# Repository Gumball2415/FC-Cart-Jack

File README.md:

# FC Cartridge Audio Jack

An audio jack output for unmodified RF Famicom systems.

## Instructions for installation

Upcoming!

## PCB Specifications

Note that this project is optimized for JLCPCB manufacturing, so you may have to modify the gerber export, remove the "JLCJLCJLCJLC" silkscreen text, etc.

- 2 layers
- 97.0mm x 64.3mm
- 1.2mm thickness
- ENIG-RoHS surface finish recommended; Gold fingers optional
- dark silkscreen, light soldermask

## License

The PCB and schematics are licensed under the [TAPR Open Hardware License](https://tapr.org/the-tapr-open-hardware-license/). © Persune 2022

## Credits

- [@N-SPC700](https://github.com/N-SPC700) for suggesting this idea
- [@Lockster-Inc](https://github.com/Lockster-Inc) for the wonderful silkscreen art
- lidnariq, Finny: advice for terminating audio output
- Finny: buffer circuit design, based on reverse engineered RF modulator schematics
- Special thanks to the NESDEV community, this project wouldn't have been possible without their extensive help and wiki.

## Support

If you enjoy this project or find it helpful, please support me on [Ko-Fi](https://ko-fi.com/persune) or [Patreon](https://www.patreon.com/persune)!

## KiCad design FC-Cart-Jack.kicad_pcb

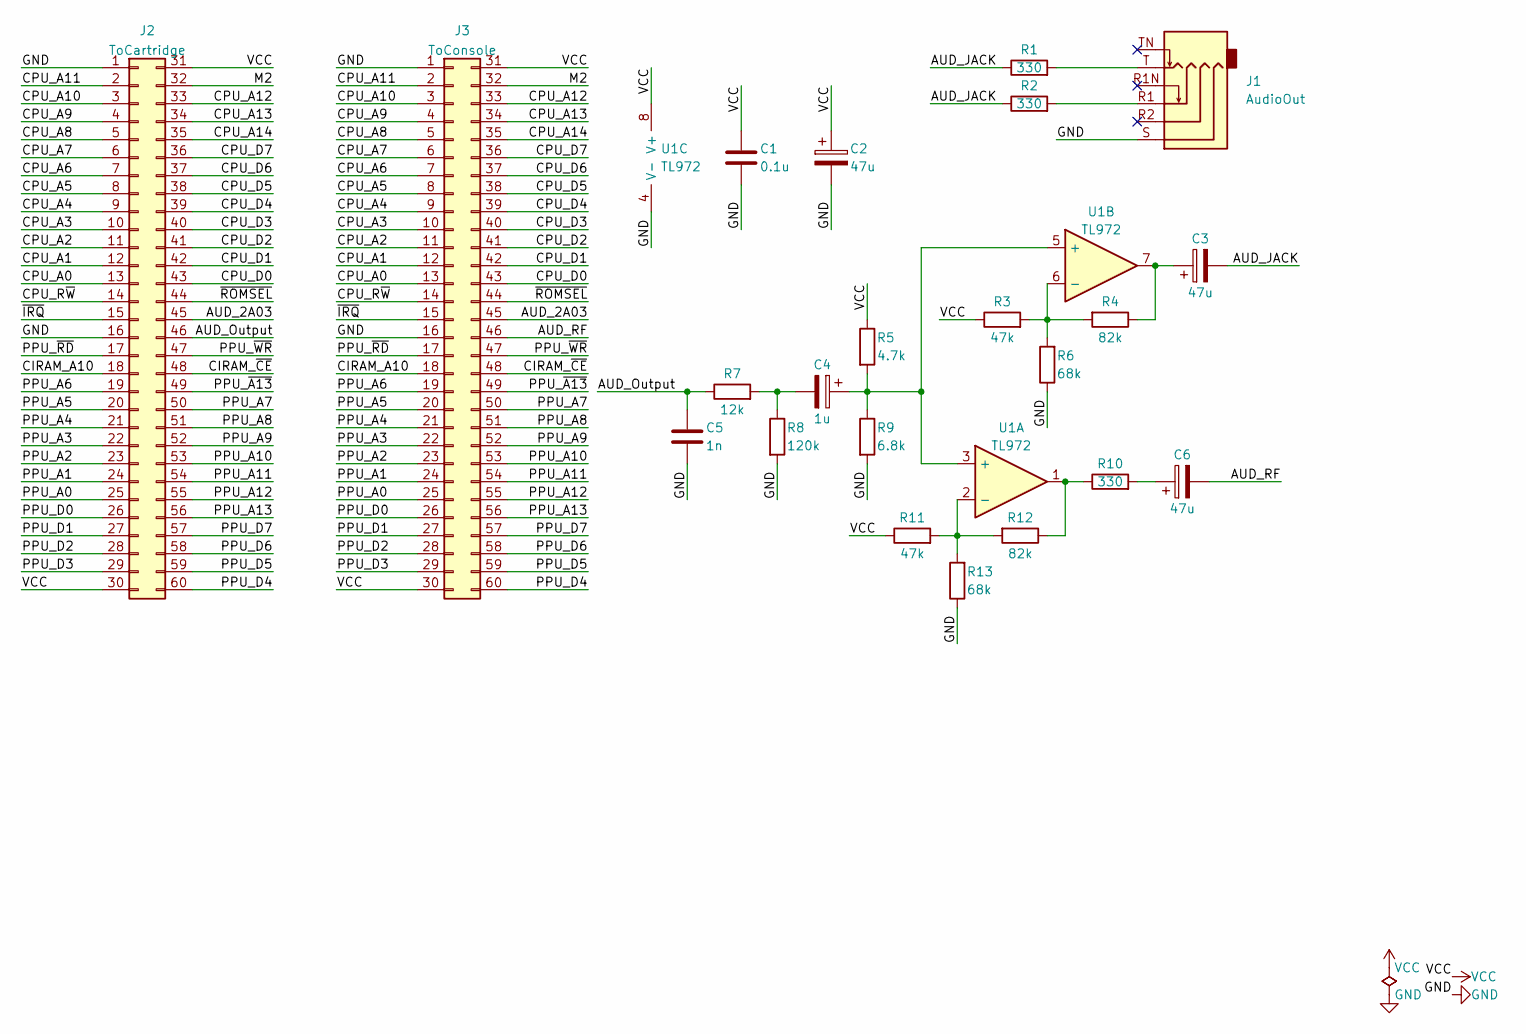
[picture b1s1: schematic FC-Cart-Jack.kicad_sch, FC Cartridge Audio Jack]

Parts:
C1: 0.1u; C_0805_2012Metric
C2, C3, C6: 47u; CP_Elec_5x5.4
C4: 1u; CP_Elec_4x5.4
C5: 1n; C_0805_2012Metric
J1: AudioOut; Jack_3.5mm_PJ-342B-TX-SMT
J2: ToCartridge; FC_CONN_F
J3: ToConsole; HVC-TGROM-01
R1, R2, R10: 330; R_0805_2012Metric
R3, R11: 47k; R_0805_2012Metric
R4, R12: 82k; R_0805_2012Metric
R5: 4.7k; R_0805_2012Metric
R6, R13: 68k; R_0805_2012Metric
R7: 12k; R_0805_2012Metric
R8: 120k; R_0805_2012Metric
R9: 6.8k; R_0805_2012Metric
U1: TL972; SO-8_3.9x4.9mm_P1.27mm

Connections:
/AUD_2A03: J2.45, J3.45
/AUD_JACK: C3.2, R1.1, R2.1
/AUD_Output: C5.1, J2.46, R7.1
/AUD_RF: C6.2, J3.46
/CIRAM_A10: J2.18, J3.18
/CIRAM_~CE: J2.48, J3.48
/CPU_A0: J2.13, J3.13
/CPU_A1: J2.12, J3.12
/CPU_A2: J2.11, J3.11
/CPU_A3: J2.10, J3.10
/CPU_A4: J2.9, J3.9
/CPU_A5: J2.8, J3.8
/CPU_A6: J2.7, J3.7
/CPU_A7: J2.6, J3.6
/CPU_A8: J2.5, J3.5
/CPU_A9: J2.4, J3.4
/CPU_A10: J2.3, J3.3
/CPU_A11: J2.2, J3.2
/CPU_A12: J2.33, J3.33
/CPU_A13: J2.34, J3.34
/CPU_A14: J2.35, J3.35
/CPU_D0: J2.43, J3.43
/CPU_D1: J2.42, J3.42
/CPU_D2: J2.41, J3.41
/CPU_D3: J2.40, J3.40
/CPU_D4: J2.39, J3.39
/CPU_D5: J2.38, J3.38
/CPU_D6: J2.37, J3.37
/CPU_D7: J2.36, J3.36
/CPU_R~W: J2.14, J3.14
/M2: J2.32, J3.32
/PPU_A0: J2.25, J3.25
/PPU_A1: J2.24, J3.24
/PPU_A2: J2.23, J3.23
/PPU_A3: J2.22, J3.22
/PPU_A4: J2.21, J3.21
/PPU_A5: J2.20, J3.20
/PPU_A6: J2.19, J3.19
/PPU_A7: J2.50, J3.50
/PPU_A8: J2.51, J3.51
/PPU_A9: J2.52, J3.52
/PPU_A10: J2.53, J3.53
/PPU_A11: J2.54, J3.54
/PPU_A12: J2.55, J3.55
/PPU_A13: J2.56, J3.56
/PPU_D0: J2.26, J3.26
/PPU_D1: J2.27, J3.27
/PPU_D2: J2.28, J3.28
/PPU_D3: J2.29, J3.29
/PPU_D4: J2.60, J3.60
/PPU_D5: J2.59, J3.59
/PPU_D6: J2.58, J3.58
/PPU_D7: J2.57, J3.57
/PPU_~A13: J2.49, J3.49
/PPU_~RD: J2.17, J3.17
/PPU_~WR: J2.47, J3.47
/~IRQ: J2.15, J3.15
/~ROMSEL: J2.44, J3.44
GND: C1.2, C2.2, C5.2, J1.S, J2.1, J2.16, J3.1, J3.16, R6.1, R8.2, R9.2, R13.1, U1.4 (V-)
unnamed: C3.1, R4.1, U1.7
unnamed: C4.2, R7.2, R8.1
unnamed: C6.1, R10.2
unnamed: J1.R1, R2.2
unnamed: J1.T, R1.2
unnamed: R10.1, R12.1, U1.1
unnamed: C4.1, R5.2, R9.1, U1.3 (+), U1.5 (+)
unnamed: R11.2, R12.2, R13.2, U1.2 (-)
unnamed: R3.2, R4.2, R6.2, U1.6 (-)
VCC: C1.1, C2.1, J2.30, J2.31, J3.30, J3.31, R3.1, R5.1, R11.1, U1.8 (V+)

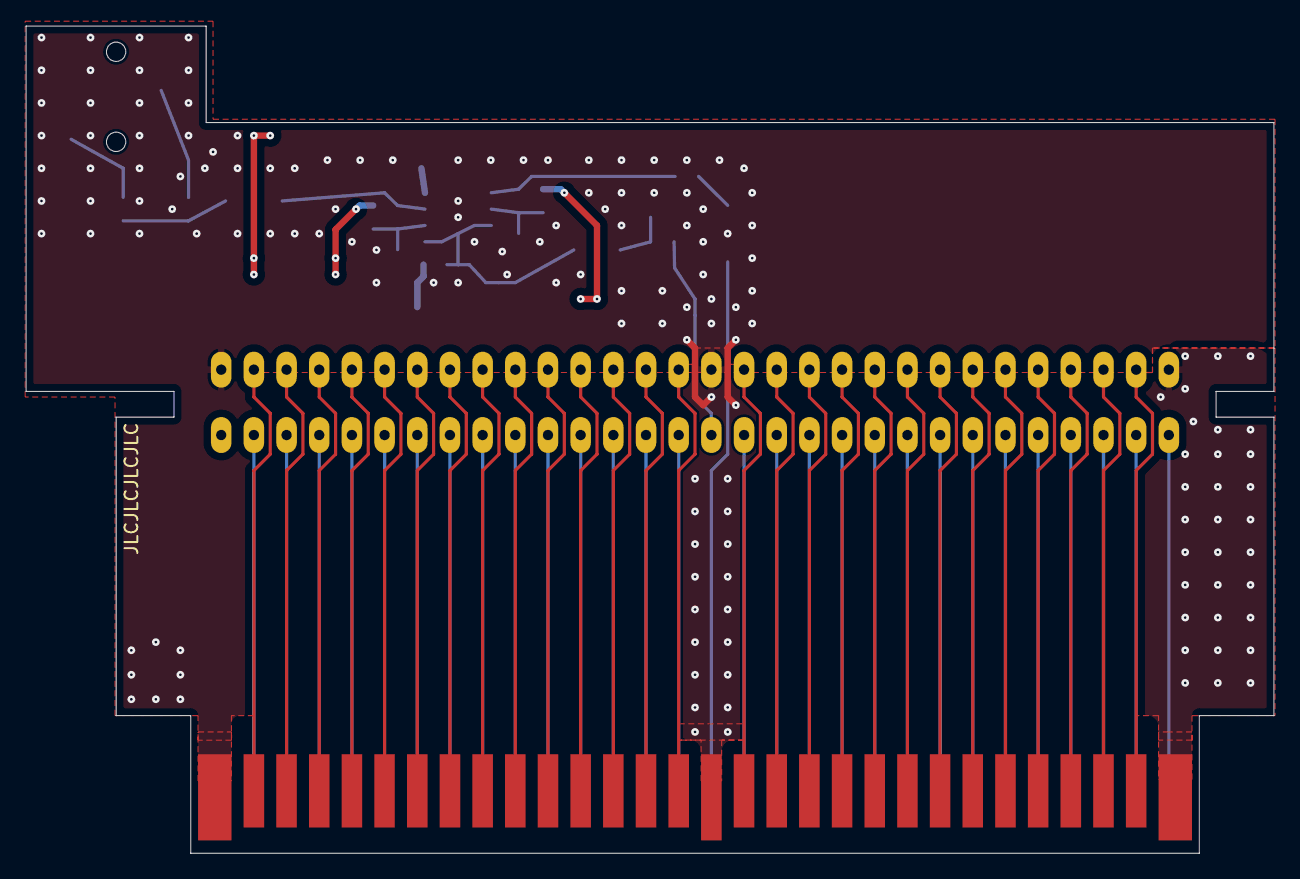
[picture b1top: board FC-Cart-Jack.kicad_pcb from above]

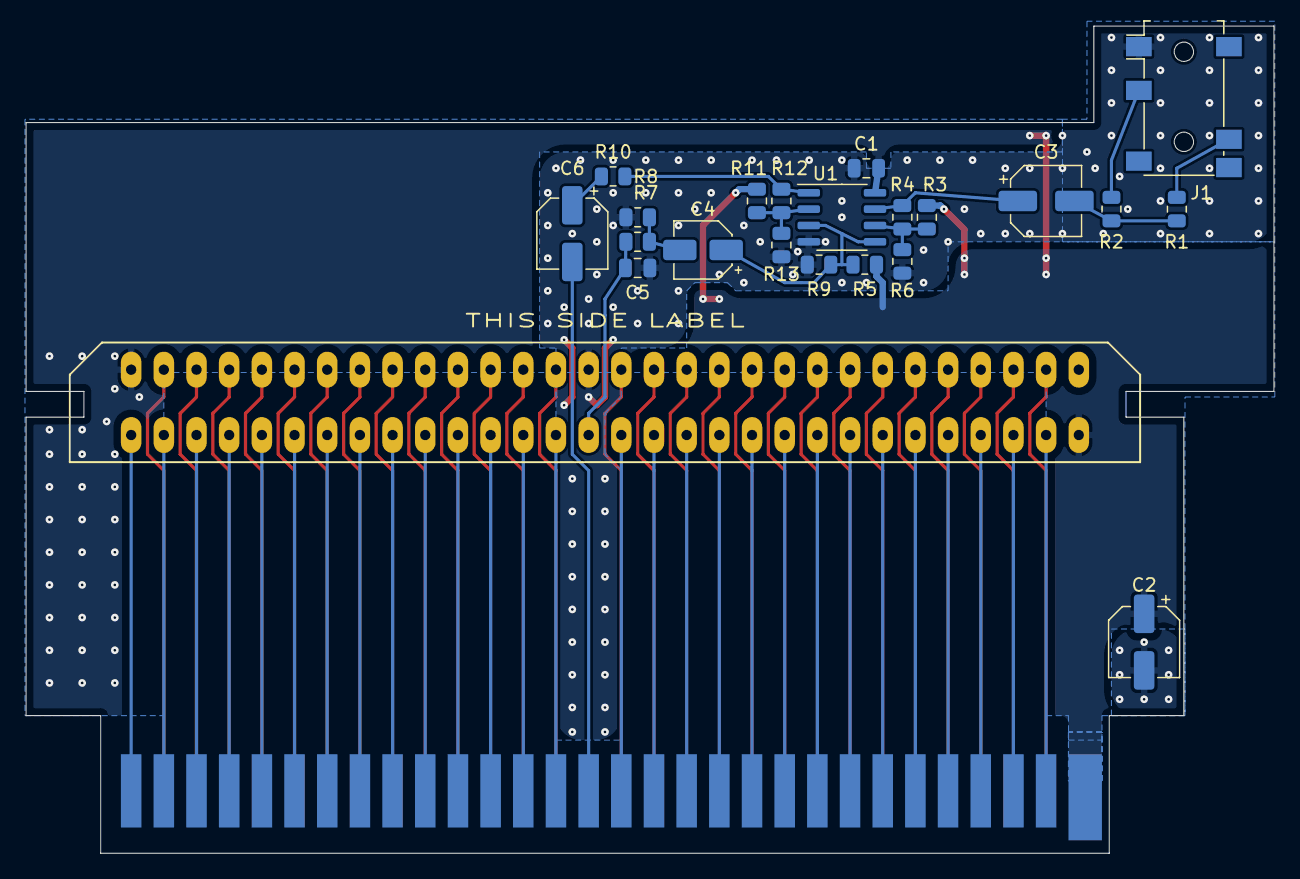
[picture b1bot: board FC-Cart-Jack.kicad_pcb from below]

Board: 2 copper layers, 97.0 x 64.3 mm, 23 parts (22 on the bottom side), 69 nets.

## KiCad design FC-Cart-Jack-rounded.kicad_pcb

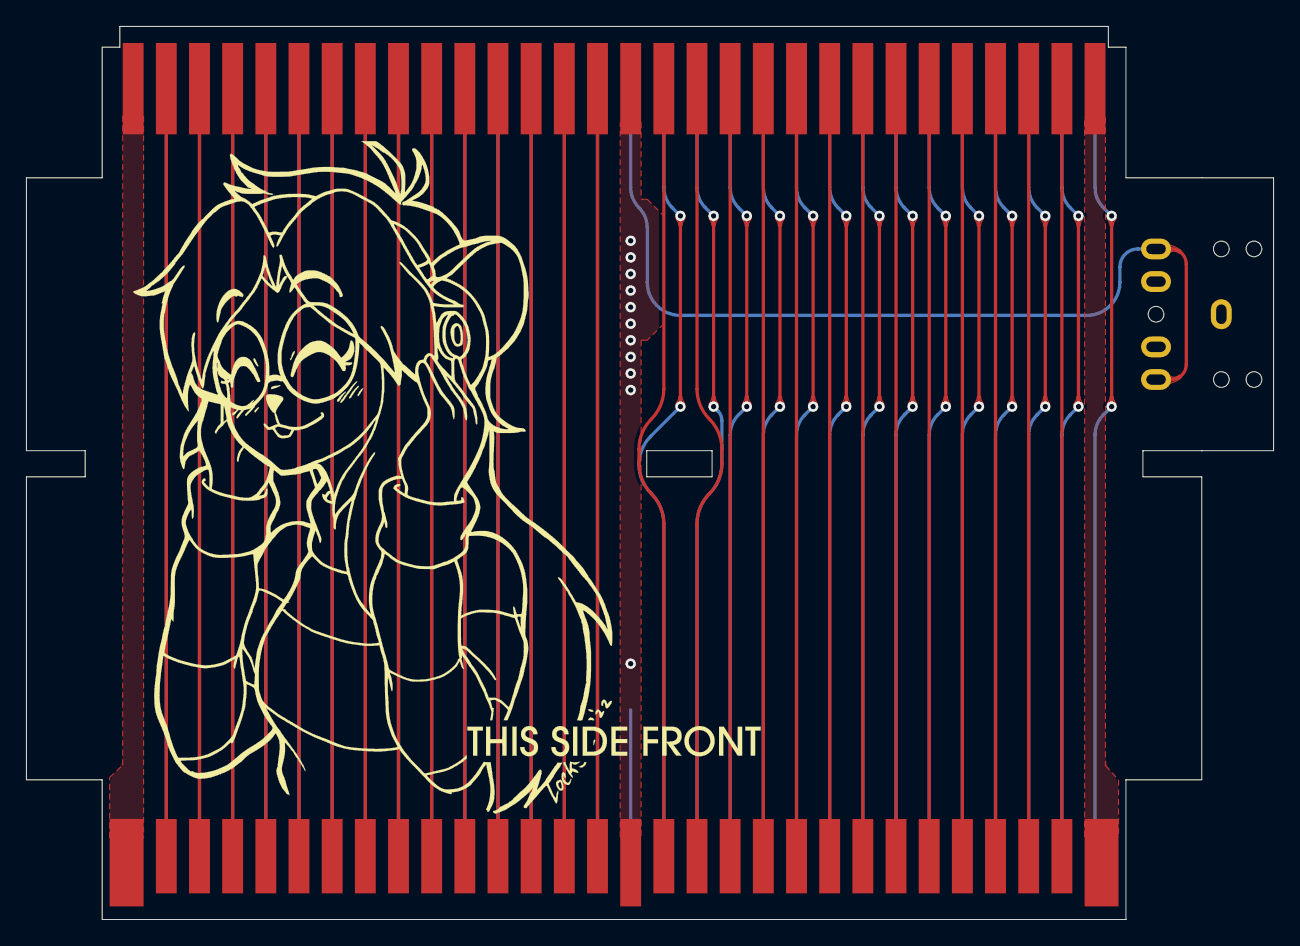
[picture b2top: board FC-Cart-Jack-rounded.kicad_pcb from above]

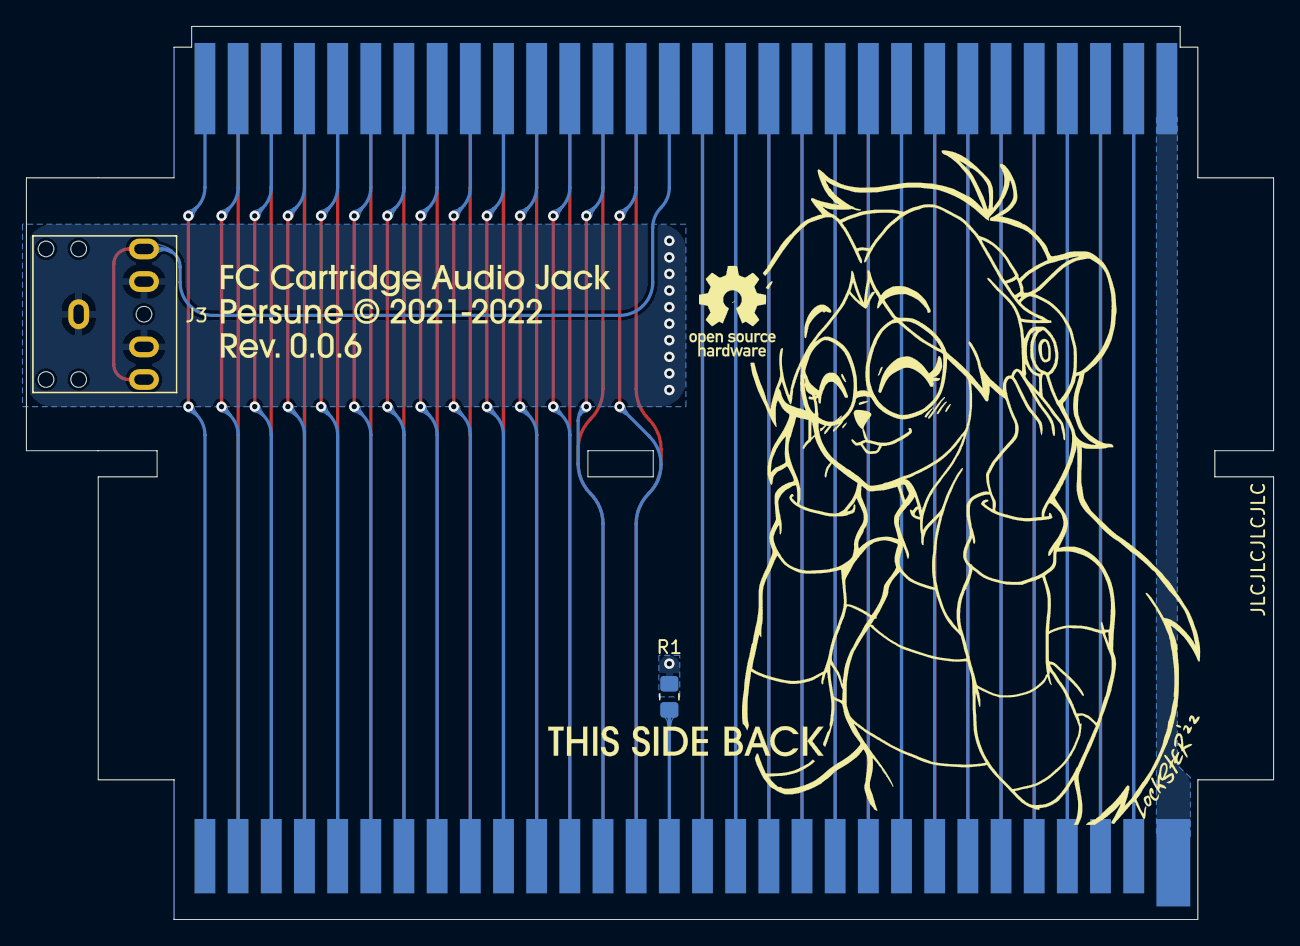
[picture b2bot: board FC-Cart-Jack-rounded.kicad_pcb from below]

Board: 2 copper layers, 95.5 x 68.4 mm, 5 parts (2 on the bottom side), 59 nets.

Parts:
J1: ToCartridge; card edge
J2: ToConsole; HVC-TGROM-01
J3: SJ1-3524NG
R1: 100K; R_0805_2012Metric_Pad1.20x1.40mm_HandSolder
Ref**: Val**; FC-Cart-Jack-rounded-brd

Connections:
/AUD_2A03: J1.45, J2.45
/AUD_Output: J1.46, J3.R, J3.T
/AUD_RF: J2.46, R1.1
/CIRAM_A10: J1.18, J2.18
/CIRAM_~CE: J1.48, J2.48
/CPU_A0: J1.13, J2.13
/CPU_A1: J1.12, J2.12
/CPU_A2: J1.11, J2.11
/CPU_A3: J1.10, J2.10
/CPU_A4: J1.9, J2.9
/CPU_A5: J1.8, J2.8
/CPU_A6: J1.7, J2.7
/CPU_A7: J1.6, J2.6
/CPU_A8: J1.5, J2.5
/CPU_A9: J1.4, J2.4
/CPU_A10: J1.3, J2.3
/CPU_A11: J1.2, J2.2
/CPU_A12: J1.33, J2.33
/CPU_A13: J1.34, J2.34
/CPU_A14: J1.35, J2.35
/CPU_D0: J1.43, J2.43
/CPU_D1: J1.42, J2.42
/CPU_D2: J1.41, J2.41
/CPU_D3: J1.40, J2.40
/CPU_D4: J1.39, J2.39
/CPU_D5: J1.38, J2.38
/CPU_D6: J1.37, J2.37
/CPU_D7: J1.36, J2.36
/CPU_R~W: J1.14, J2.14
/M2: J1.32, J2.32
/PPU_A0: J1.25, J2.25
/PPU_A1: J1.24, J2.24
/PPU_A2: J1.23, J2.23
/PPU_A3: J1.22, J2.22
/PPU_A4: J1.21, J2.21
/PPU_A5: J1.20, J2.20
/PPU_A6: J1.19, J2.19
/PPU_A7: J1.50, J2.50
/PPU_A8: J1.51, J2.51
/PPU_A9: J1.52, J2.52
/PPU_A10: J1.53, J2.53
/PPU_A11: J1.54, J2.54
/PPU_A12: J1.55, J2.55
/PPU_A13: J1.56, J2.56
/PPU_D0: J1.26, J2.26
/PPU_D1: J1.27, J2.27
/PPU_D2: J1.28, J2.28
/PPU_D3: J1.29, J2.29
/PPU_D4: J1.60, J2.60
/PPU_D5: J1.59, J2.59
/PPU_D6: J1.58, J2.58
/PPU_D7: J1.57, J2.57
/PPU_~A13: J1.49, J2.49
/PPU_~RD: J1.17, J2.17
/PPU_~WR: J1.47, J2.47
/~IRQ: J1.15, J2.15
/~ROMSEL: J1.44, J2.44
GND: J1.1, J1.16, J2.1, J2.16, J3.RN, J3.S, J3.TN, R1.2
VCC: J1.30, J1.31, J2.30, J2.31

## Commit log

2021-12-29 Revision 0.0.1
2021-12-29 Set gerber settings
2022-01-05 Add silkscreen art
    Dagga illustration by @Lockster-Inc
2022-11-14 Leave audio out floating
2022-11-14 Optionally terminate audio with 100K resistor
2022-11-30 Add FUNDING.yml
2023-04-05 Reword funding readme
2023-09-27 Add new buffer circuit
2023-09-27 Fix readme
